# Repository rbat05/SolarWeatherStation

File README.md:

# SolarWeatherStation
An end-to-end, off-grid IoT environmental telemetry system featuring custom hardware, low-power RF bridging, and a retro LCD-themed web dashboard.

<p align="center">
  
  <br>
  <em>Solar Weather Station Exterior (left) and Dashboard (right)</em>
</p>

## Table of Contents

1. [Overview](#overview)
2. [Features](#features)
3. [Performance](#performance)
4. [Design Showcase](#design-showcase)
5. [Bill of Materials](#bill-of-materials)
6. [System Architecture](#system-architecture)
7. [Firmware & Code](#firmware--code)
8. [3D-Printed Parts](#3d-printed-parts)
9. [License](#license)

---

## 1. Overview
The **Solar Weather Station** is a completely custom-engineered, three-tier IoT ecosystem designed to capture, transmit, and visualize highly accurate micro-climate data. 

>Currently measures **temperature**, **humidity**, **absolute pressure**, and **battery voltage** at 30 seconds intervals.

Operating entirely off-grid, the remote sensor node utilizes solar power and aggressive deep-sleep optimizations to monitor environmental conditions indefinitely. To bypass the extreme battery drain of standard WiFi, it broadcasts lightweight packets via ESP-NOW to a continuously powered indoor Relay node. This Relay acts as a bridge, forwarding the data into a local Python Flask server where it is logged, archived, and displayed on a visually striking, retro-commercial LCD-style dashboard.

## 2. Features
* **100% Off-Grid Operation:** Powered by a localized solar charging circuit and Li-Po battery.
* **Decoupled RF Architecture:** Uses a low-latency, low-power ESP-NOW to WiFi bridge, saving massive amounts of battery life compared to direct-to-router connections.
* **Bulletproof Failsafes:** Features hardware brownout bypassing, local SD card data logging, offline memory buffering (RTC memory), and relay rate-limited backfilling so data is never lost during network dropouts.
* **Retro LCD Dashboard:** A beautiful, responsive, bespoke green-and-black dot-matrix web interface built with pure HTML/JS, Flask, and SQLite.
* **Historical Replay Engine:** A dual-database architecture allows you to dynamically load archived CSV data into a sandbox database to "replay" historical weather events on the dashboard without interrupting the live data stream.
* **Local vs. Regional Analytics:** Automatically fetches regional telemetry from the Open-Meteo API to compare your micro-climate directly against metropolitan averages.

## 3. Performance
Aggressive power-saving techniques were implemented in the ESP32 C++ firmware. By throttling the clock speed down to 80MHz, actively forcing the WiFi/Bluetooth modems off during boot initialization, and removing parasitic hardware LEDs (like the one on the DS3231 RTC), the remote station achieves incredible efficiency:

* **Average Active Time:** < 8.0 seconds per wake cycle.
* **Average Active Current:** ~60 mA (Peak during SD Write & ESP-NOW transmission).
* **Average Sleep Current:** ~2.5 mA.
* **Weighted Average Draw:** ~4.03 mA over a standard cycle.

This ultra-low consumption allows the station to easily survive extended periods of heavy cloud cover without dropping below critical battery voltages.

## 4. Design Showcase

- **Mechanical Design:** Custom 3D-printed Stevenson Screen with integrated mounting points for the PCB and solar panel. The solar panel sits at a 35-degree angle to maximize sun exposure (in Auckland, NZ) while the louvers provide airflow to ensure accurate sensor readings.
  <p align="center">
    <br>
    <em>3D-Printed Stevenson Screen Render</em>
  </p>

- **Internal Assembly:** Custom PCB secured inside the Stevenson Screen.
  <p align="center">
    <br>
    <em>Custom PCB Mounted Inside Enclosure</em>
  </p>

- **LCD Dashboard:** A retro-inspired web interface displaying real-time and historical weather data.

**Dashboard Features:**

- **Live Mode:** Continuously streams real-time environmental data directly from the local SQLite database.
  <p align="center">
    <br>
    <em>Main Dashboard View (Live Mode)</em>
  </p>

- **Historical Replay Engine:** Dynamically loads archived 7-day CSV files into a sandbox database to replay historical weather events without interrupting live data ingestion. Can set custom timeframes to analyze specific events (e.g., a storm).
  <p align="center">
    <br>
    <em>Replaying Historical Sandbox Data</em>
  </p>

- **Local vs. Regional Comparison:** Automatically polls regional telemetry from the Open-Meteo API to compare your micro-climate directly against metropolitan averages (displayed alongside the "Today" summary).
  <p align="center">
    <br>
    <em>Local Micro-climate vs. Regional Averages</em>
  </p>

- **Summary Statistics:** Provides actionable insights and rolling statistics (High, Low, Average) across different timeframes:
  - **Today:** Current day metrics.
  - **Yesterday:** A rolling 24-hour window to spot diurnal patterns.
  - **72 Hours & 7 Days:** Extended views to analyze multi-day weather events and trends.

- **Interactive Graphing:** Powered by Chart.js, the interactive graph can map individual metrics over adjustable time-scales (1 hour, 3 hours, 12 hours, 24 hours, 72 hours, or 7 days):
  - **Temperature**
  - **Humidity**
  - **Absolute Pressure**
  - **Battery Voltage**
  <p align="center">
    <br>
    <em>Interactive 7-Day Telemetry Chart</em>
  </p>

## 5. Bill of Materials
### Remote Weather Station
* **Microcontroller:** ESP32 (Throttled to 80MHz)
* **Environmental Sensor:** BME280 (Temperature, Humidity, Absolute Pressure)
* **Real-Time Clock:** DS3231 (Hardware power LED physically removed for power savings)
* **Storage:** MicroSD Card Module (SPI)
* **Power:** Solar Panel, TP4056 (or equivalent) Charge Controller, 3.7v Li-Po/18650 Battery

### Indoor Relay Node
* **Microcontroller:** ESP8266

### Local Server
* **Hardware:** Any local machine (e.g., Raspberry Pi) capable of running Python 3.

## 6. System Architecture
The system is broken into three distinct operational layers:

1. **Layer 1: Edge Telemetry (Weather Station)** 
   Wakes up on an interval timer, samples the BME280 and battery voltage, writes to the local SD card, and fires a rapid ESP-NOW string to the Relay before returning to deep sleep. For a detailed breakdown, see the [Weather Station README](./code/WeatherStationCode/README.md).
2. **Layer 2: Network Bridge (Relay Node)** 
   Stays awake permanently on mains power. Listens for the ESP-NOW MAC address. Upon receiving a packet, it formats it into a JSON payload and executes an HTTP POST request over the home WiFi network. For a detailed breakdown, see the [Relay Node README](./code/RelayCode/README.md).
3. **Layer 3: Data Ingestion & Visualization (Dashboard)** 
   A Python Flask server operating on a local machine. It intercepts the HTTP POST at the `/ingest` endpoint, commits the data to an SQLite database, handles infinite 7-day auto-archiving to CSV, and serves the UI. For a detailed breakdown, see the [Dashboard README](./code/DashboardCode/README.md).

## 7. Firmware & Code
The codebase is heavily modularized across three main directories. Please refer to their individual `README.md` files for deep dives into their logic.

* **`/code/WeatherStationCode`:** 
  C++ (PlatformIO) for the remote ESP32. Handles aggressive power management, hardware watchdog failsafes, I2C/SPI bus management, and RTC memory buffering.
* **`/code/RelayCode`:** 
  C++ (PlatformIO) for the indoor ESP8266. Features a non-blocking `millis()` architecture, in-memory offline packet buffering, auto-WiFi reconnections, and OTA flashing support.
* **`/code/DashboardCode`:** 
  Python/Flask backend and HTML/JS frontend. Handles the API endpoints, Open-Meteo polling, database querying, and the retro Chart.js interactive graph rendering.

## 8. Custom Hardware Integration
### Custom PCB (`/pcb`)
Rather than relying on messy jumper wires and breadboards, the Weather Station relies on a completely custom-designed Printed Circuit Board. This custom PCB integrates the ESP32, charge controllers, and sensor headers into a single, reliable footprint. This minimizes point-of-failure wire disconnects, reduces electrical noise on the I2C/SPI busses, and provides a perfectly dimensioned mounting solution for the 3D-printed case. Designed using KiCAD 10.

### 3D-Printed Parts (`/cad`)
All physical enclosures for the project were custom modeled in CAD to fit the bespoke electronics and withstand the elements.

* **Stevenson Screen (Weather Station):** 
  A classic multi-louvered meteorological enclosure. It is specifically designed to shield the BME280 sensor from direct UV radiation and precipitation while allowing ambient wind/air to freely pass through. This prevents artificial greenhouse heating inside the case, ensuring the temperature readings are a true reflection of the outside air. Provided a .step file for easy modification of the full assembly in any CAD software.
* **Low-Profile Relay Case:** 
  This enclosure can be found at [Makerworld](https://makerworld.com/en/models/58547-nodemcu-v2-cp2102-cover#profileId-60347). Credit to Lyron for the original design. A hole was cut on the top for the heatsink.

## 9. License
This project is licensed under the GNU General Public License v3.0 (GPL-3.0).

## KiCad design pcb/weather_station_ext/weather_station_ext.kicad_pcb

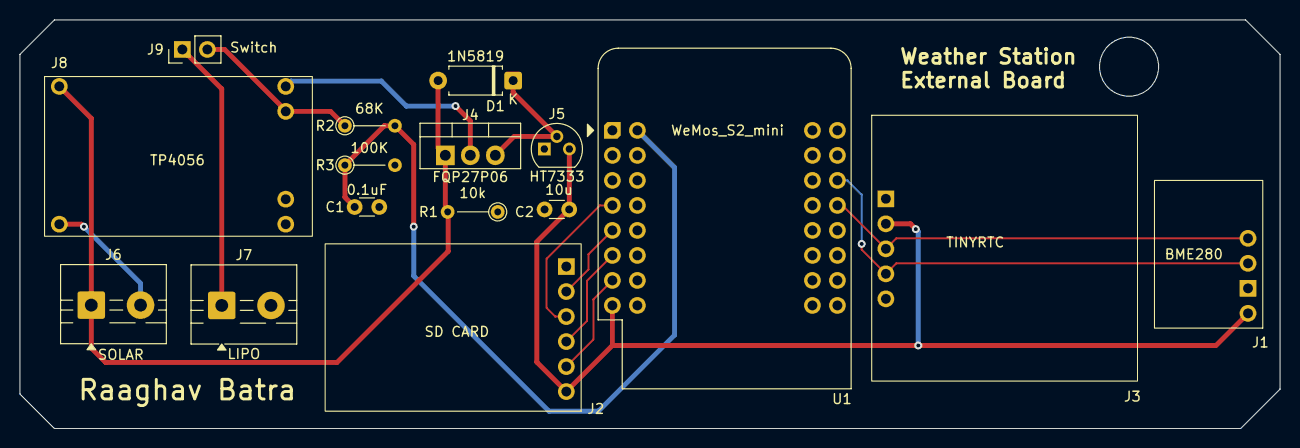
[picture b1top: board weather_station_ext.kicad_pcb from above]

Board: 2 copper layers, 128.0 x 41.5 mm, 16 parts (0 on the bottom side), 14 nets.

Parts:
C1: 0.1uF; C_Disc_D3.0mm_W1.6mm_P2.50mm
C2: 10u; C_Disc_D3.0mm_W1.6mm_P2.50mm
D1: 1N5819; D_A-405_P7.62mm_Horizontal
J1: BME280; PinSocket_1x04_P2.54mm_Vertical
J2: SD; PinSocket_1x06_P2.54mm_Vertical
J3: TINYRTC; PinSocket_1x05_P2.54mm_Vertical
J4: FQP27P06; TO-220-3_Vertical
J5: HT7333; TO-92
J6: SOLAR; TerminalBlock_MaiXu_MX126-5.0-02P_1x02_P5.00mm
J7: LIPO; TerminalBlock_MaiXu_MX126-5.0-02P_1x02_P5.00mm
J8: TP4056; PinHeader_1x06_P2.54mm_Vertical
J9: Switch; PinHeader_1x02_P2.54mm_Vertical
R1: 10k; R_Axial_DIN0204_L3.6mm_D1.6mm_P5.08mm_Vertical
R2: 68K; R_Axial_DIN0204_L3.6mm_D1.6mm_P5.08mm_Vertical
R3: 100K; R_Axial_DIN0204_L3.6mm_D1.6mm_P5.08mm_Vertical
U1: WeMos_S2_mini; wemoss2

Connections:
/3V3: C2.1, J1.1 (3V3), J2.1 (3V3), J3.2 (3V3), J5.3 (OUT), U1.8 (3V3)
/CS: J2.2 (CS), U1.7 (GPIO12)
/GND: C1.2, C2.2, J1.2 (GND), J2.6 (GND), J3.1 (GND), J5.1 (GND), J7.2 (GND), J8.4 (OUT-), J8.6 (B-), R1.1, R3.2, U1.10 (GND), U1.26 (GND)
/IN+: D1.2 (A), J4.1 (GATE), J6.1 (VSOLAR), J8.1 (IN+), R1.2
/IN-: J6.2 (GND), J8.2 (IN-)
/MISO: J2.5 (MISO), U1.5 (GPIO9)
/MOSI: J2.3 (MOSI), U1.6 (GPIO11)
/OUT+: J4.2 (DRAIN), J8.3 (OUT+)
/SCK: J2.4 (CLK), U1.4 (GPIO7)
/SCL: J1.3 (SCL), J3.4 (SCL), U1.14 (GPIO35)
/SDA: J1.4 (SDA), J3.3 (SDA), U1.13 (GPIO33)
/VBATT: C1.1, R2.2, R3.1, U1.17 (GPIO1)
/VLIPO: J7.1 (VLIPO), J8.5 (B+), J9.1 (VLIPO), J9.2 (VLIPO), R2.1
unnamed: D1.1 (K), J4.3 (SOURCE), J5.2 (IN)

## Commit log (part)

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2024-12-28 Modified Readme
2024-12-30 Readme update, logbook new file created.
2024-12-30 Created code library, established communication with microcontroller.
2025-01-04 Created seperate files for different sensors.
2025-01-04 BME280 sensor setup and get values functions written.
2025-01-04 Functions to put bme280 into sleep and normal mode written.
2025-01-05 UV sensor functionality code written.
2025-01-05 RTC functions written.
2025-01-17 Wrote new utilities file, small changes here and there after testing.
2025-01-18 Implemented 100x data sampling for bme280. Wrote code for writing data to sd card, tested and fully working.
2025-02-02 24HR test worked, multiple small changes.
2025-02-02 Renamed main folder
2025-02-03 Functionality for head unit achieved (display live time with latest readings) but in a crude way.
2025-02-04 Sampling battery voltage readings, shortened days. Modularised head unit code.
2025-02-04 Unified code style to camelCase.
2025-02-07 Got rid of UV sensor code, sensor too unreliable. New data logging format, create new file daily. Code cleanup.
2025-02-08 Weather station to head unit communication working :)))
2025-02-08 Code cleanup. Weather station code finalised for current hardware. Head Unit needs webserver.
2025-02-10 Working webserver, ESPNOW comms, data logging. Implemented landing page with daily stats, updated everytime new reading is sent. Fixed brownout stability issues.
2025-03-03 Readme updated.
2025-03-03 Readme update
2025-07-11 Readme update, added updated wiring diagram
2025-07-11 Update LICENSE
2025-07-13 Added images to repo, added WIP note.
2026-04-26 some images
2026-04-27 made new rtc module work.
2026-04-30 implemented safety features in case sd or sensor failure
2026-04-30 changed to more accurate rtc module
2026-05-04 made headunit be a relay to a server, removed all other func. added buffer to main station, if esp now fails
2026-05-04 added ota support, removed channel fixing in weather station
2026-05-04 reorganised repo
2026-05-04 fixed esp now issues, station now sends data to relay, relay can handle http post and ota updates
2026-05-05 weather station dashboard initial version
2026-05-05 developed app2 and 3. 2 is 90s weather summary. 3 is lcd screen. 3 is peak btw. both better than app.py.
2026-05-06 dashboard working as wanted, working on splitting into live mode and replay mode.
2026-05-06 its fine i guess, cant make large gaps display using dotted lines. good for now
2026-05-06 name change to dashboard
2026-05-06 nuked old readme shit, need to add images.
2026-05-06 readme updates
2026-05-09 created static showcase for dashboard
2026-05-09 mobile freindly, ready to go
2026-05-11 good to go showcase
2026-05-13 readme updated with images. waiting for full day data run

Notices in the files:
README.md:
License: GPL v3
